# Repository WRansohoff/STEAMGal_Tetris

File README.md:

# Overview

This is firmware for a 'tetris' game on a 'STEAMGal' board driven by an STM32 chip.

# Current Status

Incomplete. The firmware initializes the system clock to 48MHz driven by the HSI oscillator, then draws a simple menu to the OLED screen.

It sets up hardware interrupts for each of the 6 buttons - the 'A' button selects the test menu's start menu to start the game, and the 'Up' button returns to the menu from within the game. I'm hoping to add a 'pause' menu, though.

The onboard LED blinks on and off each game 'tick', which causes the current block to drop if it can, and fix in place on the grid if not. A 'game over' happens when a brick gets fixed in place while part of it is above the top line. Rows are cleared if necessary when a brick is fixed in place.

But there's no scoring, the game doesn't get faster as it progresses, there's no "next brick" display, etc. Just the basics.

Currently, only the STM32F051K8 is supported, but I hope to add the STM32F303K8 as well if time permits.

# Board Design

The board design is available under the 'board\_design\_v0' directory. It includes a circuit for 30-pin 128x64 SSD1306 monochrome OLED screens which seems to work, although I did crib that from the cheap 4-pin screen modules you can get off of ebay/aliexpress/etc for a few bucks. I've gotten several slightly different boards like that, and they all seem to use roughly the same design. Some of them omit the diode in the reset circuit, but since the screen has an onboard charge pump to generate a display bias voltage higher than 3.3V, I figure better safe than sorry.

Here's the first version of the board as rendered by OshPark. It seems to work as expected, but the ribbon connection is just barely close enough to the cutout to fold the screen over; I'll be moving that a bit in the next revision, along with adding an EEPROM chip. Also, the buzzer is sort of loud; I should probably add a potentiometer for volume control.

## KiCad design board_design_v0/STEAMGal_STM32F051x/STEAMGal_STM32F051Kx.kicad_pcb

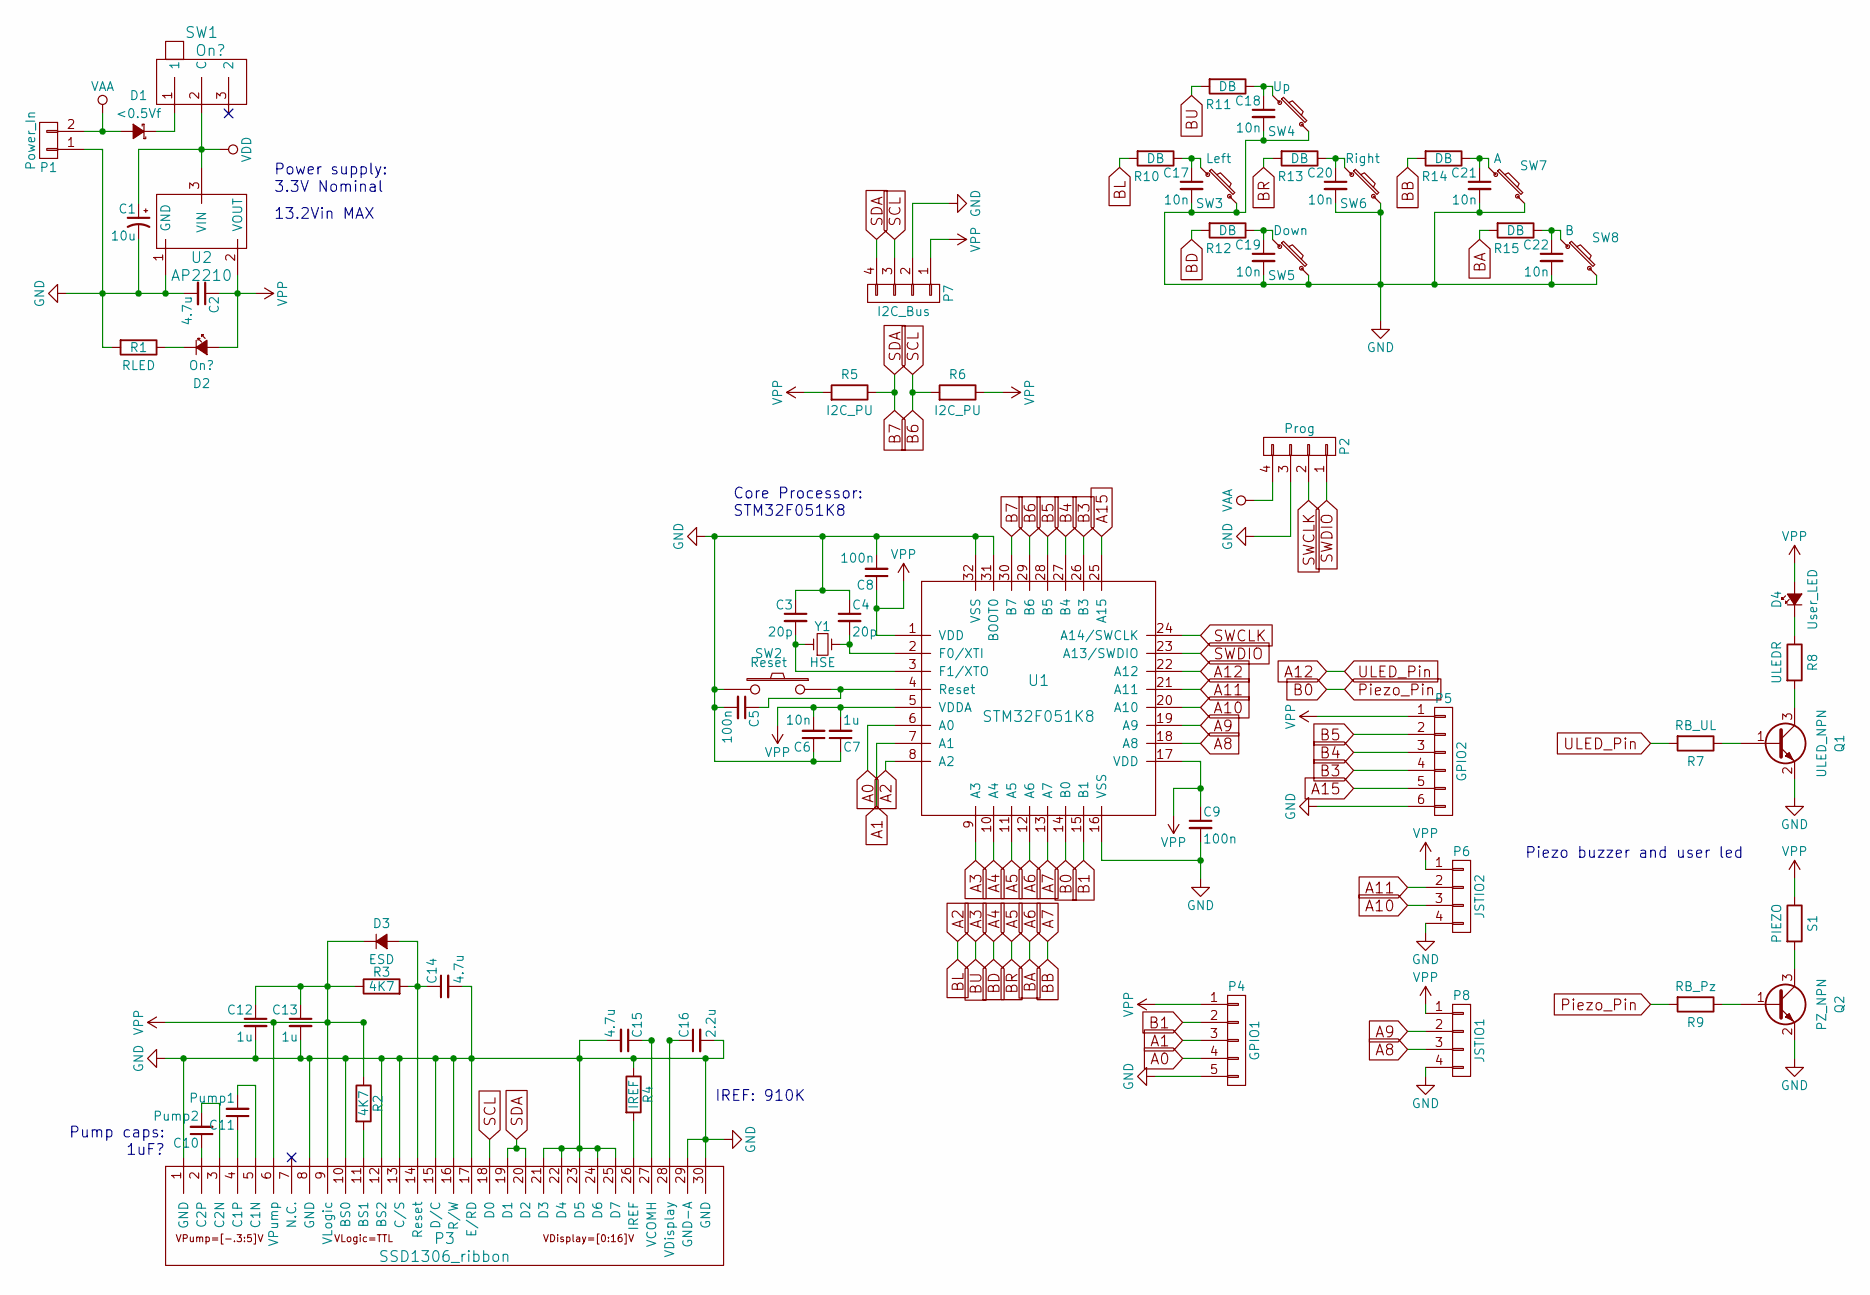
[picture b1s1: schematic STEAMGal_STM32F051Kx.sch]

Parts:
C1: 10u; TantalC_SizeA_EIA-3216_HandSoldering
C2, C14, C15: 4.7u; C_0805_HandSoldering
C3, C4: 20p; C_0603_HandSoldering
C5, C8, C9: 100n; C_0805_HandSoldering
C6, C17, C18, C19, C20, C21, C22: 10n; C_0805_HandSoldering
C7, C12, C13: 1u; C_0805_HandSoldering
C10: Pump2; C_0805_HandSoldering
C11: Pump1; C_0805_HandSoldering
C16: 2.2u; C_0805_HandSoldering
D1: <0.5Vf; SOD-123
D2: On?; LED_0805
D3: ESD; SOD-123
D4: User_LED; LED_0805
P1: Power_In; Pin_Header_Angled_1x02
P2: Prog; Pin_Header_Angled_1x04
P3: SSD1306_ribbon; SSD1306_Raw
P4: GPIO1; Pin_Header_Straight_1x05
P5: GPIO2; Pin_Header_Straight_1x06
P6: JSTIO2; JST_PH_2.0-4
P7: I2C_Bus; Pin_Header_Straight_1x04
P8: JSTIO1; JST_PH_2.0-4
Q1: ULED_NPN; SOT-23_Handsoldering
Q2: PZ_NPN; SOT-23_Handsoldering
R1: RLED; R_0805_HandSoldering
R2, R3: 4K7; R_0805_HandSoldering
R4: IREF; R_0805_HandSoldering
R5, R6: I2C_PU; R_0805_HandSoldering
R7: RB_UL; R_0805_HandSoldering
R8: ULEDR; R_0805_HandSoldering
R9: RB_Pz; R_0805_HandSoldering
R10, R11, R12, R13, R14, R15: DB; R_0805_HandSoldering
S1: PIEZO; Piezo_Buzzer_Mini
SW1: On?; SPDT_Slide_SMD_RA
SW2: Reset; Button_SMD_2L_3x6x2.5mm
SW3: Left; Button_SMD_2L_3x6x2.5mm
SW4: Up; Button_SMD_2L_3x6x2.5mm
SW5: Down; Button_SMD_2L_3x6x2.5mm
SW6: Right; Button_SMD_2L_3x6x2.5mm
SW7: A; Button_SMD_2L_3x6x2.5mm
SW8: B; Button_SMD_2L_3x6x2.5mm
U1: STM32F051K8; LQFP-32_7x7mm_Pitch0.8mm_HandSoldering
U2: AP2210; SOT-23_Handsoldering
Y1: HSE; XTAL_HF_2SMD_1

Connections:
A0: P4.4, U1.6 (A0)
A1: P4.3, U1.7 (A1)
A2: R10.2, U1.8 (A2)
A3: R11.2, U1.9 (A3)
A4: R12.2, U1.10 (A4)
A5: R13.2, U1.11 (A5)
A6: R15.2, U1.12 (A6)
A7: R14.2, U1.13 (A7)
A8: P8.3, U1.18 (A8)
A9: P8.2, U1.19 (A9)
A10: P6.3, U1.20 (A10)
A11: P6.2, U1.21 (A11)
A12: R7.2, U1.22 (A12)
A15: P5.5, U1.25 (A15)
B0: R9.2, U1.14 (B0)
B1: P4.2, U1.15 (B1)
B3: P5.4, U1.26 (B3)
B4: P5.3, U1.27 (B4)
B5: P5.2, U1.28 (B5)
B6: P3.18 (D0), P7.3, R6.2, U1.29 (B6)
B7: P3.19 (D1), P3.20 (D2), P7.4, R5.1, U1.30 (B7)
GND: C1.2, C2.2, C3.1, C4.1, C5.2, C6.1, C7.1, C8.2, C9.2, C12.2, C13.2, C14.2, C15.2, C16.2, C17.2, C18.2, C19.2, C20.2, C21.2, C22.2, P1.1, P2.3, P3.1 (GND), P3.8 (GND), P3.10 (BS0), P3.12 (BS2), P3.13 (C/S), P3.15 (D/C), P3.16 (R/W), P3.17 (E/RD), P3.21 (D3), P3.22 (D4), P3.23 (D5), P3.24 (D6), P3.25 (D7), P3.29 (GND-A), P3.30 (GND), P4.5, P5.6, P6.4, P7.2, P8.4, Q1.2 (E), Q2.2 (E), R1.2, R4.1, SW2.2, SW3.2, SW4.2, SW5.2, SW6.2, SW7.2, SW8.2, U1.16 (VSS), U1.31 (BOOT0), U1.32 (VSS), U2.1 (GND)
unnamed: C3.2, U1.3 (F1/XTO), Y1.1
unnamed: C4.2, U1.2 (F0/XTI), Y1.2
unnamed: C5.1, SW2.1, U1.4 (Reset)
unnamed: C10.1, P3.2 (C2P)
unnamed: C10.2, P3.3 (C2N)
unnamed: C11.1, P3.4 (C1P)
unnamed: C11.2, P3.5 (C1N)
unnamed: C14.1, D3.2 (A), P3.14 (Reset), R3.2
unnamed: C15.1, P3.27 (VCOMH)
unnamed: C16.1, P3.28 (VDisplay)
unnamed: C17.1, R10.1, SW3.1
unnamed: C18.1, R11.1, SW4.1
unnamed: C19.1, R12.1, SW5.1
unnamed: C20.1, R13.1, SW6.1
unnamed: C21.1, R14.1, SW7.1
unnamed: C22.1, R15.1, SW8.1
unnamed: D1.1 (K), SW1.1
unnamed: D2.1 (K), R1.1
unnamed: D4.1 (K), R8.1
unnamed: P3.11 (BS1), R2.2
unnamed: P3.26 (IREF), R4.2
unnamed: Q1.1 (B), R7.1
unnamed: Q1.3 (C), R8.2
unnamed: Q2.1 (B), R9.1
unnamed: Q2.3 (C), S1.2
SWCLK: P2.2, U1.24 (A14/SWCLK)
SWDIO: P2.1, U1.23 (A13/SWDIO)
VAA: D1.2 (A), P1.2, P2.4
VDD: C1.1, SW1.2 (C), U2.3 (VIN)
VPP: C2.1, C6.2, C7.2, C8.1, C9.1, C12.1, C13.1, D2.2 (A), D3.1 (K), D4.2 (A), P3.6 (VPump), P3.9 (VLogic), P4.1, P5.1, P6.1, P7.1, P8.1, R2.1, R3.1, R5.2, R6.1, S1.1, U1.1 (VDD), U1.5 (VDDA), U1.17 (VDD), U2.2 (VOUT)

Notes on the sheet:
Pump caps: 1uF?
IREF: 910K
Piezo buzzer and user led
Core Processor: STM32F051K8
Power supply: 3.3V Nominal
13.2Vin MAX

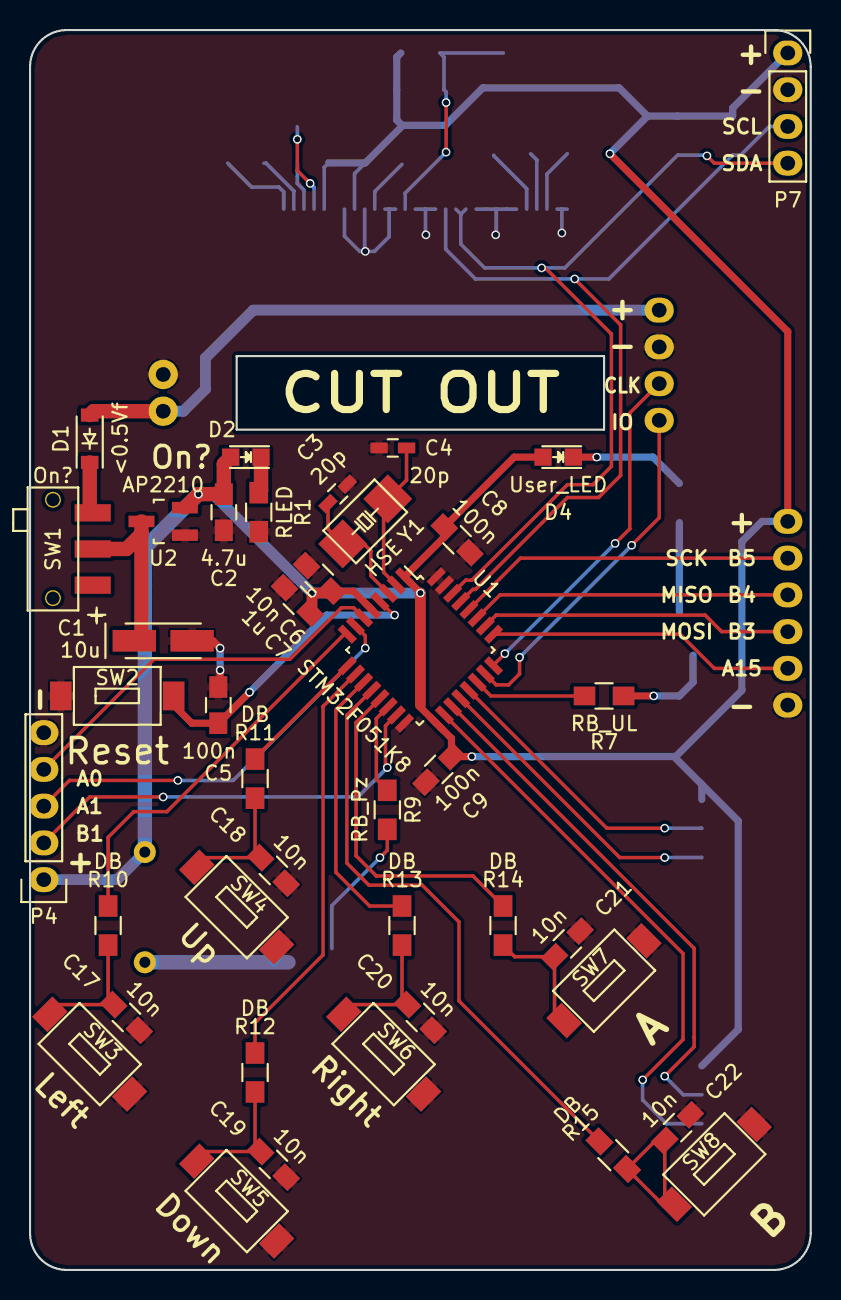
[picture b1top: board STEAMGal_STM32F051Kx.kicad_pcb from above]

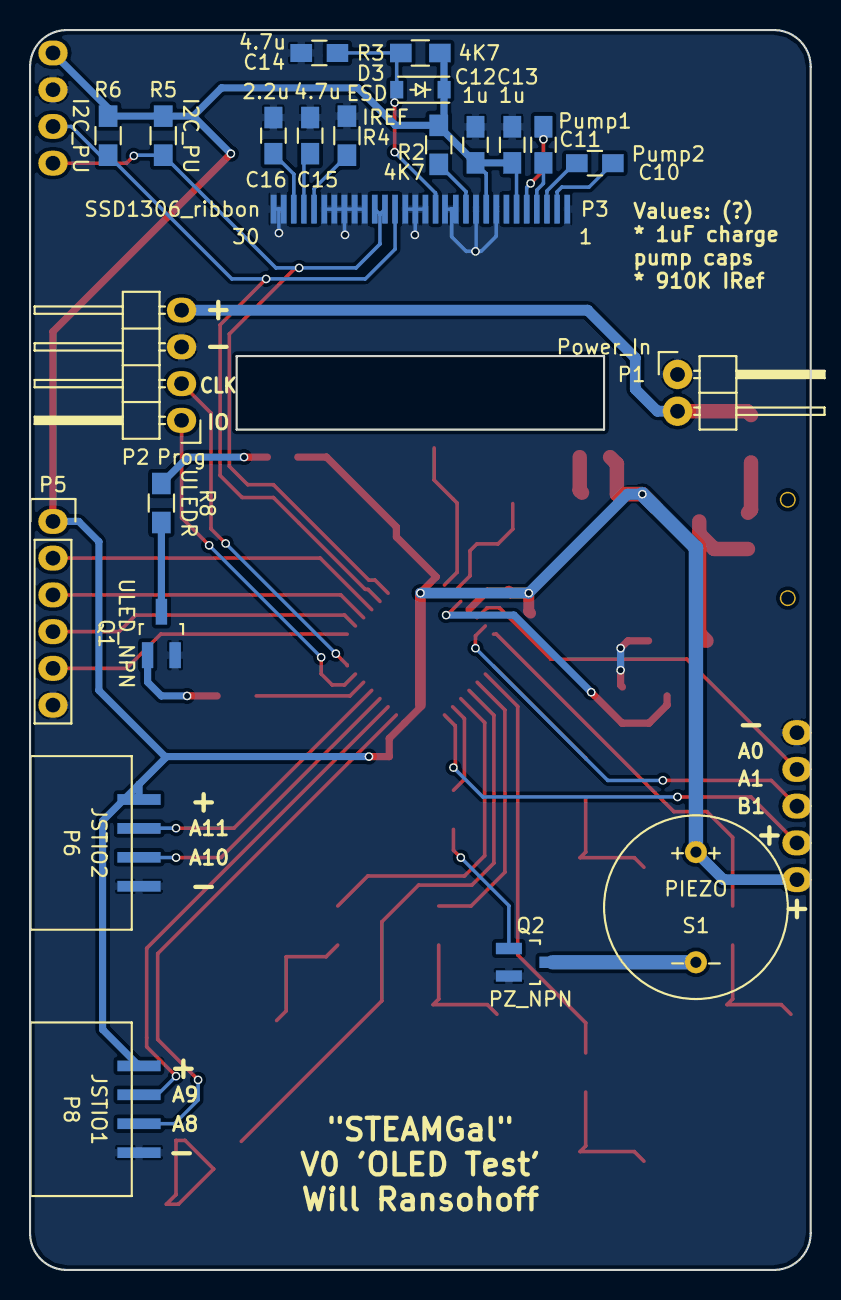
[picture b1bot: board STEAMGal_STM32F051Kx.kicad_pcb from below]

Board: 2 copper layers, 54.0 x 85.7 mm, 63 parts (23 on the bottom side), 52 nets.

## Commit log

2018-05-01 Initial commit: Just some basic test firmware.
2018-05-02 Add a 'peripherals' file for common peripherals commands, and add a timer peripheral to test doing game 'steps' on a timer
2018-05-03 Move I2C methods from Thumb assembly to C.
2018-05-03 Whoops, update the readme.
2018-05-03 Add a constant array to define the tetris bricks - I bet you could just read the un-rotated bricks in different 'directions' to avoid storing rotations, but...it's like 42 extra bytes. Also inline so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
2018-05-06 Add a simple 'game loop' which drops the current block by one position if possible. If not, the brick is fixed in the grid and a new one added. But still no controls and it's just the 'I' brick.
2018-05-06 Add a 'game over' screen when bricks reach the top.
2018-05-06 Add 'left/right' button interrupt handlers to move the current brick left or right.
2018-05-06 Add block rotation.
2018-05-06 Add pseudo-random brick types.
2018-05-06 Add row-clearing logic. I think this is now a bare-bones, but technically working, tetris-like game!
